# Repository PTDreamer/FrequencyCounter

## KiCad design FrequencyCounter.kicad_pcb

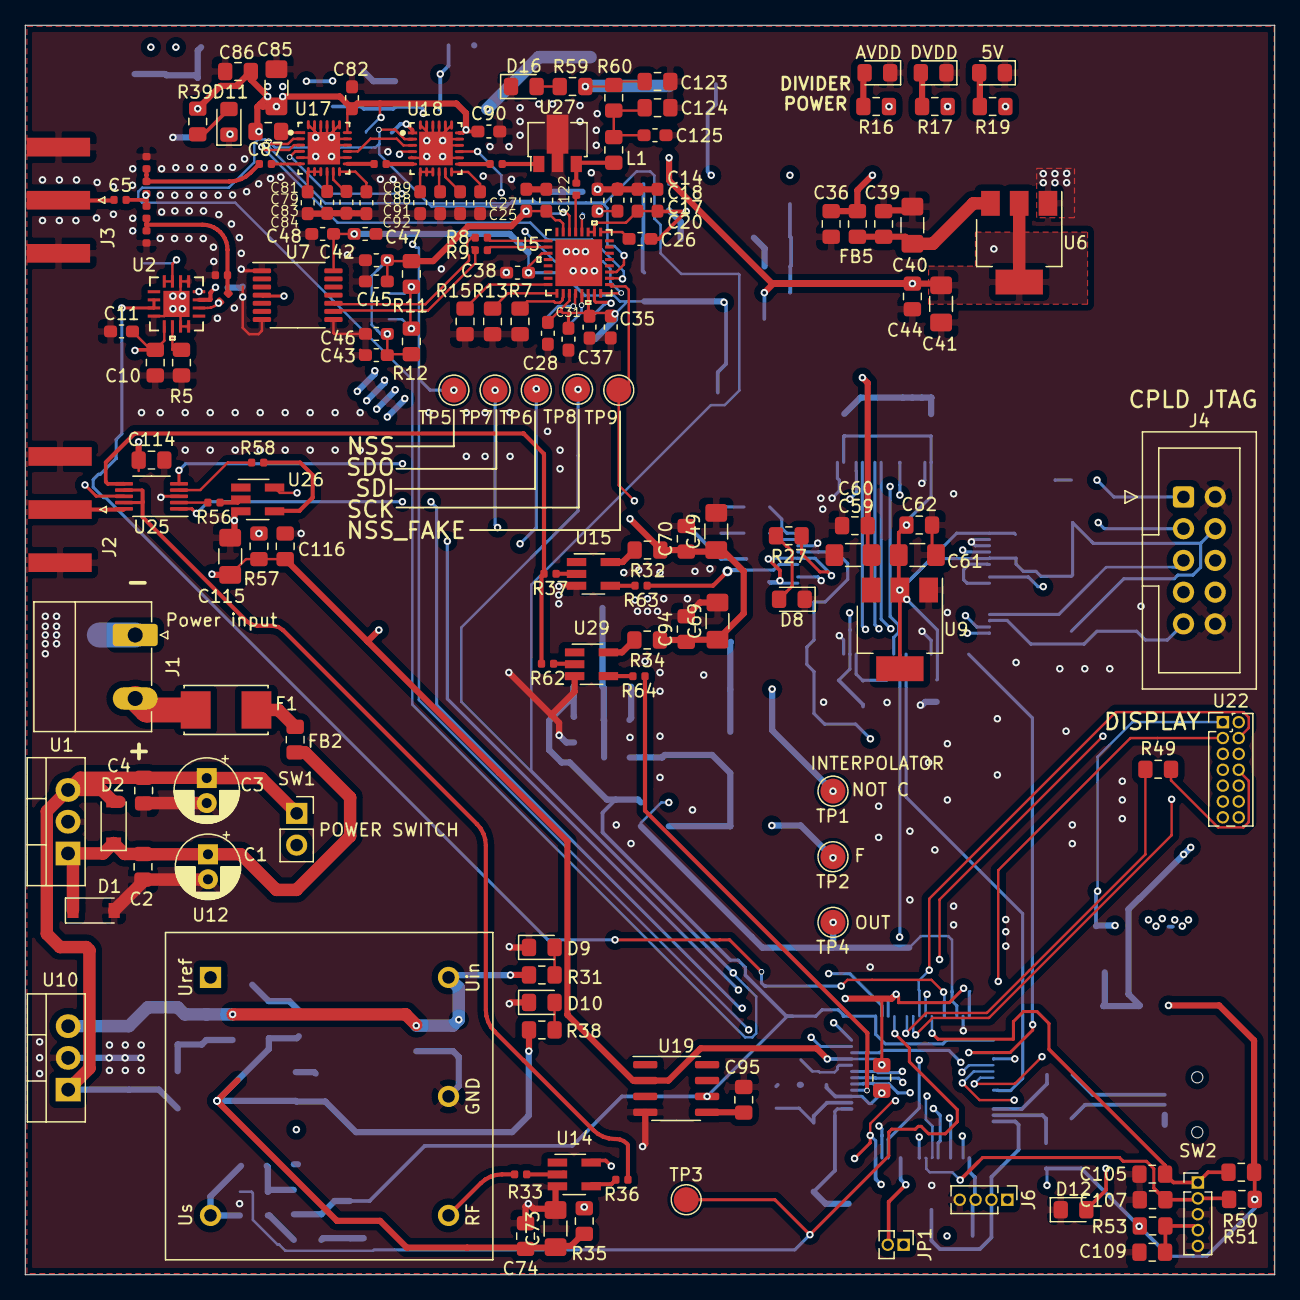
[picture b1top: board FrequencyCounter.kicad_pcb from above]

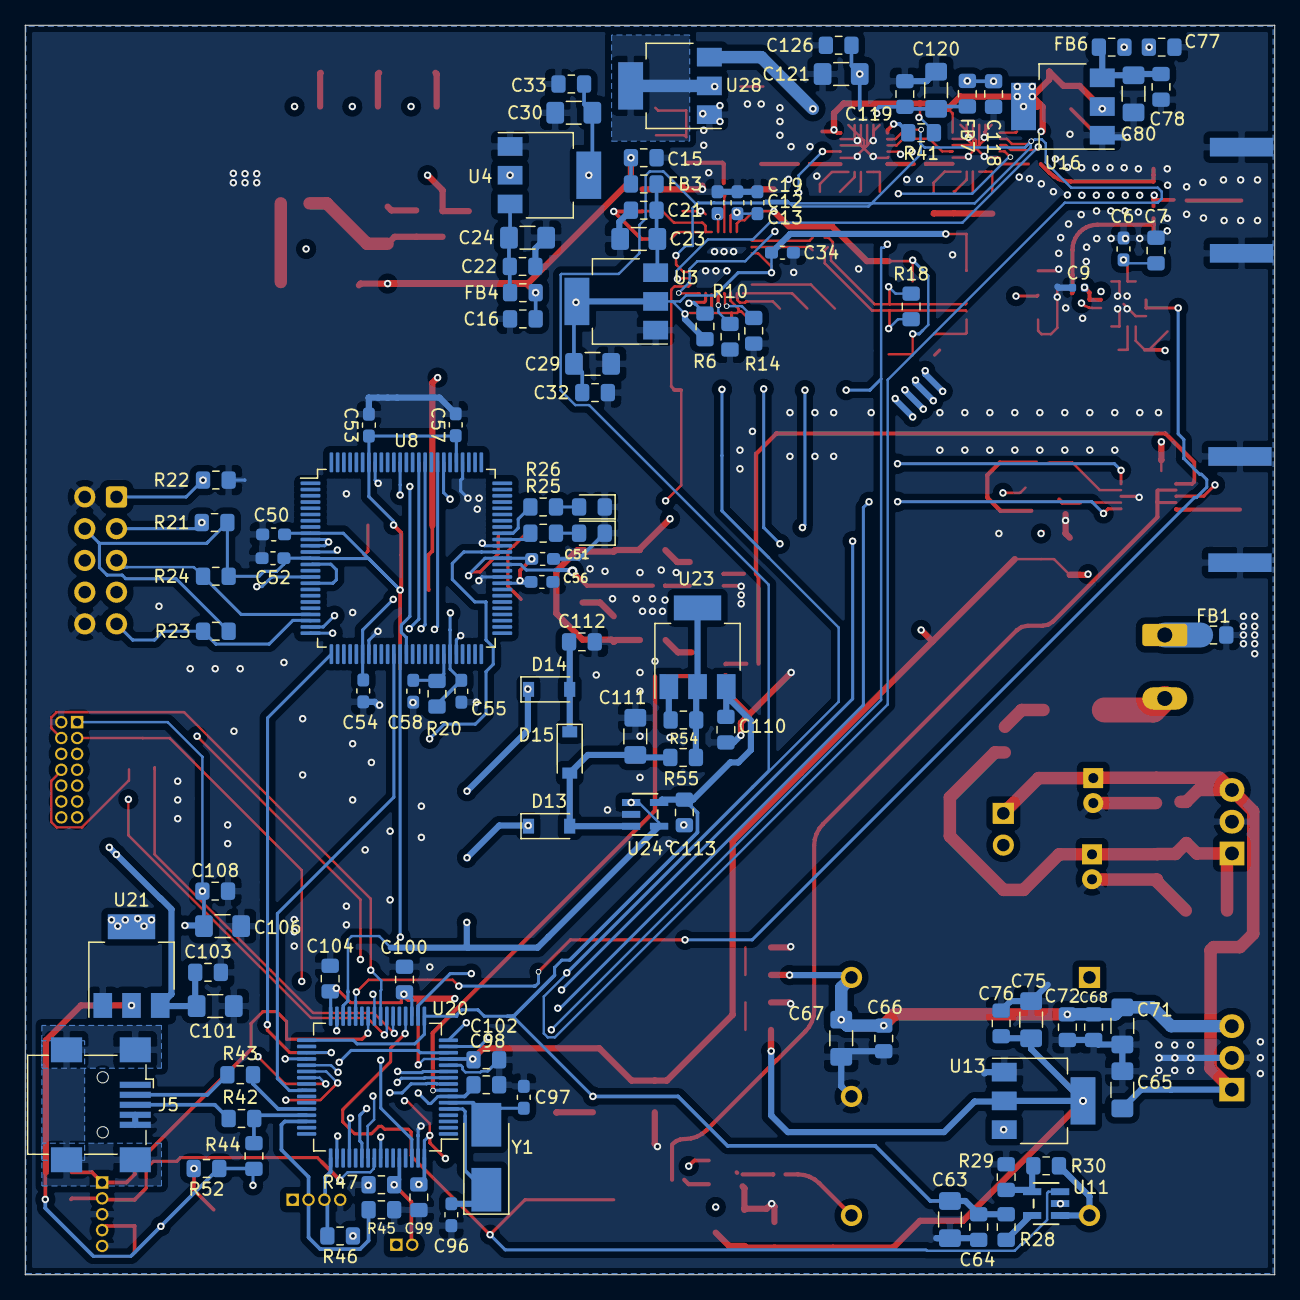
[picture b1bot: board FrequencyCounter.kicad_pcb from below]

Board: 4 copper layers, 100.0 x 100.0 mm, 263 parts (106 on the bottom side), 150 nets.

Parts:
C1, C3: 10u; CP_Radial_D5.0mm_P2.00mm
C2, C4: 10n; C_0805_2012Metric_Pad1.15x1.40mm_HandSolder
C5: 10n; C_0402_1005Metric
C6, C11, C13, C18, C19, C20, C27, C31, C35, C38: 100p; C_0603_1608Metric_Pad1.05x0.95mm_HandSolder
C7, C10, C15, C16, C21, C22, C32, C33, C36, C39, C44, C60, C62, C64, C66, C68, C70, C72, C74, C76, C77, C78, C86, C94, C98, C99, C100, C102, C103, C104, C108, C114, C116, C118, C119, C126: 0.1u; C_0805_2012Metric_Pad1.15x1.40mm_HandSolder
C8, C9: 1n; C_0402_1005Metric
C12, C14, C17, C25, C28, C34, C37, C42, C43, C47, C50, C51, C52, C53, C54, C55, C56, C57, C58: 0.1u; C_0603_1608Metric_Pad1.05x0.95mm_HandSolder
C23, C24, C29, C30, C40, C41, C80, C85, C120, C121: 10u; C_1206_3216Metric_Pad1.42x1.75mm_HandSolder
C26, C45, C46: 0.001u; C_0603_1608Metric_Pad1.05x0.95mm_HandSolder
C48: 0.01u; C_0603_1608Metric_Pad1.05x0.95mm_HandSolder
C49, C63, C67, C69, C73, C111, C115: 4.7u; C_1206_3216Metric_Pad1.42x1.75mm_HandSolder
C59, C61, C71, C75, C101, C106: 22u; C_1206_3216Metric_Pad1.42x1.75mm_HandSolder
C65: 0.33u; C_1206_3216Metric_Pad1.42x1.75mm_HandSolder
C79, C81, C83, C84, C88, C89, C91, C92: 330p; C_0603_1608Metric_Pad1.05x0.95mm_HandSolder
C82, C90: 1n; C_0603_1608Metric_Pad1.05x0.95mm_HandSolder
C87, C93: 330p; C_0402_1005Metric
C95, C110, C123: 1u; C_0805_2012Metric_Pad1.15x1.40mm_HandSolder
C96, C97: 8p; C_0603_1608Metric_Pad1.05x0.95mm_HandSolder
C105, C107, C109, C113: 100n; C_0805_2012Metric_Pad1.15x1.40mm_HandSolder
C112: 1n; C_0805_2012Metric_Pad1.15x1.40mm_HandSolder
C117, C122: 100n; C_0402_1005Metric
C124: 1.2n; C_0805_2012Metric_Pad1.15x1.40mm_HandSolder
C125: 68p; C_0603_1608Metric_Pad1.05x0.95mm_HandSolder
D1, D2: D; D_SOD-123
D3, D4, D5, D6, D7, D8, D9, D10, D11, D12, D16: LED; D_0805_2012Metric_Pad1.15x1.40mm_HandSolder
D13, D14, D15: 1N4148W; D_SOD-123
F1: Fuse; Fuseholder_Littelfuse_Nano2_157x
FB1, FB2, FB3, FB4, FB5, FB6, FB7: Ferrite_Bead; L_0805_2012Metric_Pad1.15x1.40mm_HandSolder
J1: Power input; PhoenixContact_MC_1,5_2-G-5.08_1x02_P5.08mm_Horizontal
J2: Ref_Imput; SMA_Amphenol_132289_EdgeMount
J3: Conn_Coaxial; SMA_Amphenol_132289_EdgeMount
J4: Microsemi_FlashPro-JTAG-10; IDC-Header_2x05_P2.54mm_Vertical
J5: USB_B_Micro; USB_Mini-B_Wuerth_65100516121_Horizontal
J6: SWD; PinHeader_1x04_P1.27mm_Vertical
JP1: Jumper_NO_Small; PinHeader_1x02_P1.27mm_Vertical
L1: 43nH; L_0805_2012Metric_Pad1.15x1.40mm_HandSolder
R1, R3: 1200; R_0402_1005Metric
R2: 4.12; R_0402_1005Metric
R4, R61: 52.3; R_0402_1005Metric
R5: 499; R_0805_2012Metric_Pad1.15x1.40mm_HandSolder
R6, R40, R41, R47: 100K; R_0805_2012Metric_Pad1.15x1.40mm_HandSolder
R7, R10, R13, R14, R15, R54: R; R_0805_2012Metric_Pad1.15x1.40mm_HandSolder
R8, R9: 24.9; R_0402_1005Metric
R11, R12: 75; R_0805_2012Metric_Pad1.15x1.40mm_HandSolder
R16, R17, R19, R25, R26, R27, R30, R38, R39, R49, R52, R59: 1K; R_0805_2012Metric_Pad1.15x1.40mm_HandSolder
R18: 100; R_0805_2012Metric_Pad1.15x1.40mm_HandSolder
R20, R21, R22, R23, R24, R45, R46, R48, R50, R51, R53: 10K; R_0805_2012Metric_Pad1.15x1.40mm_HandSolder
R28, R32, R34, R35, R57: 4.7; R_0805_2012Metric_Pad1.15x1.40mm_HandSolder
R29: 2K; R_0805_2012Metric_Pad1.15x1.40mm_HandSolder
R31: 1.8K; R_0805_2012Metric_Pad1.15x1.40mm_HandSolder
R33, R56: 49.9; R_0402_1005Metric
R36, R58, R63, R64: 33; R_0402_1005Metric
R37, R62: 100; R_0402_1005Metric
R42, R43: 20; R_0805_2012Metric_Pad1.15x1.40mm_HandSolder
R44: 1.5K; R_0805_2012Metric_Pad1.15x1.40mm_HandSolder
R55: 1R; R_0805_2012Metric_Pad1.15x1.40mm_HandSolder
R60: 0; R_0805_2012Metric_Pad1.15x1.40mm_HandSolder
SW1: SW_SPST; PinSocket_1x02_P2.54mm_Vertical
SW2: Rotary_Encoder_Switch; 1x5_1.27_rotary_encoder
TP1: INTPL_NC; TestPoint_Pad_D2.0mm
TP2: INTPL_F; TestPoint_Pad_D2.0mm
TP3: REF_ADJ_V; TestPoint_Pad_D2.0mm
TP4: INTPL_OUT; TestPoint_Pad_D2.0mm
TP5: SPI3_NSS; TestPoint_Pad_D2.0mm
TP6: SPI3_SDI; TestPoint_Pad_D2.0mm
TP7: SPI3_SDO; TestPoint_Pad_D2.0mm
TP8: SPI3_SCK; TestPoint_Pad_D2.0mm
TP9: SPI3_NSS_FAKE; TestPoint_Pad_D2.0mm
U1: LM7810_TO220; TO-220-3_Vertical
U2: AD8318ACPZ-REEL7
U3, U4, U16: LM1117-3.3; SOT-223-3_TabPin2
U5: HMC983LP5E
U6, U28: LM1117-5.0; SOT-223-3_TabPin2
U7: DS90LV019TMTC_NOPB; TSSOP-14_4.4x5mm_P0.65mm
U8: EPM240T100; LQFP-100_14x14mm_P0.5mm
U9, U13, U21: AMS1117-3.3; SOT-223-3_TabPin2
U10: LM7805_TO220; TO-220-3_Vertical
U11, U24: OPA365AIDBVT
U12: MV267; Oscillator_OCXO_Morion_MV317
U14, U15, U26, U29: NC7SZ04M5X; SOT-23-5_HandSoldering
U17, U18: HMC624ALP4E; Analog_Devices_Inc-CP-24-16-12_2017-C-0
U19: REF5025ID; SOIC-8_3.9x4.9mm_P1.27mm
U20: STM32F373R8Tx; LQFP-64_10x10mm_P0.5mm
U22: CR2013-MI2120; PinHeader_2x07_P1.27mm_Vertical
U23: LT3080xST; SOT-223
U25: TS5A23159DGS; VSSOP-10_3x3mm_P0.5mm
U27: ADL5610; SOT-89-3
Y1: 8MHz; Crystal_SMD_5032-2Pin_5.0x3.2mm_HandSoldering

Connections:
+3V3: C73.1, C74.1, C75.1, C76.1, R35.1, R38.1, U13.2
+3V3_processor: C49.1, C69.1, C70.1, C94.1, C99.1, C100.1, C102.1, C104.1, C106.1, C108.1, C114.1, C115.1, C116.1, J6.1, JP1.1, R32.1, R34.1, R44.1, R46.1, R48.1, R50.1, R51.1, R52.1, R53.1, R57.1, U19.2, U20.13, U20.19, U20.32, U20.64, U21.2, U22.1, U25.8
+5V: C66.1, C67.1, C68.1, C71.1, C72.1, R31.1, U10.3, U12.5, U13.3
/VCC: C36.1, C59.1, C60.1, C77.1, C101.1, C103.1, C118.1, FB5.1, FB6.1, FB7.1, SW1.2, U9.3, U21.3
/VCC_ALWAYS_ON: C3.1, C4.1, C65.1, D2.2, SW1.1, U1.3, U10.1
/amplifier/RF_IN: C117.2, U18.13
/attenuator/ATTEN1_SERIN: TP6.1, U5.2, U17.3, U20.18
/attenuator/ATTEN1_SEROUT: U17.15, U18.3
/attenuator/ATTEN2_SEROUT: TP7.1, U5.32, U18.15, U20.16
/attenuator/ATTEN_CLK: TP8.1, U5.3, U17.2, U18.2, U20.15
/attenuator/ATTEN_LE: TP5.1, U17.4, U18.4, U20.50
/attenuator/RF_IN: C87.1, R1.2, R2.2
/attenuator/VDD: C82.1, C85.1, C86.1, C90.1, R39.1, R40.1, R41.1, U16.2, U17.18, U18.18
/divider/5V: C15.1, C16.1, C25.1, C27.1, C41.1, C42.1, C43.1, C44.1, C45.1, C46.1, FB3.1, FB4.1, R11.2, R12.1, R19.1, U5.15, U6.2
/divider/AVDD: C12.1, C13.1, C14.1, C17.1, C18.1, C20.1, C26.2, C30.1, C33.1, R16.1, U4.2, U5.10, U5.11, U5.14
/divider/DVDD: C28.1, C29.1, C31.1, C32.1, C34.1, C35.1, C37.1, C38.1, C47.1, C48.1, R6.1, R17.1, U3.2, U5.19, U5.27, U5.30, U7.14
/divider/INPUT: C122.1, U5.13
/divider/OUT: U7.4, U8.38
/divider/SENB: TP9.1, U5.1, U20.55
/divider/div_clk_N: R8.2, U5.17
/divider/div_clk_P: R9.2, U5.18
/divider/div_clkr_N: R8.1, R11.1, R18.1, U7.10
/divider/div_clkr_P: R9.1, R12.2, R18.2, U7.9
/fpga/3.3V: C50.1, C51.1, C52.1, C53.1, C54.1, C55.1, C56.1, C57.1, C61.1, C62.1, J4.4, R20.1, R21.1, R23.1, R24.1, R27.1, U8.9, U8.13, U8.31, U8.45, U8.59, U8.63, U8.80, U8.94, U9.2
/fpga/icp0: U8.26, U20.35
/fpga/refclk: R63.1, U8.62
/fpga/sigclk: U8.14, U8.17
/frequency_ref/3.3V_ref_in: C63.1, C64.1, C110.1, C113.1, R28.1, U19.6, U20.17, U20.33, U23.3, U24.5
/frequency_ref/10MHz: R36.1, U25.7, U25.9
/interpolator/f: D13.1, TP2.1, U8.82
/interpolator/int_out: TP4.1, U20.30, U24.1, U24.4
/interpolator/not_c: D14.1, TP1.1, U8.89
/logdetector/5V_in: C6.2, C7.2, C10.2, C11.2, C121.1, C123.2, C126.1, R59.1, R60.1, U2.3, U2.4, U2.9, U2.16, U28.2
/logdetector/RF_INPUT: C8.1, R3.1, R4.1, R61.2
/processor/ADC1: U2.6, U2.7, U20.28
/processor/CLK_OUT: U8.36, U20.41
/processor/DAC1: TP3.1, U11.3, U20.20
/processor/DAC2_OUT1: R49.1, U20.22
/processor/LCD_DC: U20.25, U22.5
/processor/LCD_RESET: U20.24, U22.4
/processor/MODESHIFT: U8.16, U20.57
/processor/SPI1_CLK: U20.38, U22.7
/processor/SPI1_MISO: U20.39, U22.6
/processor/SPI1_NSS: U20.37, U22.3
/processor/SPI2_CLK: U8.12, U20.36
/processor/SPI2_MISO: U8.37, U20.10
/processor/SPI2_MOSI: U8.86, U20.11
/processor/SPI2_NSS: U8.64, U20.62
/processor/SWD_CLK: J6.3, R46.2, U20.49
/processor/SWD_IO: J6.2, R45.1, U20.46
/processor/TIM2_ETR: U8.85, U20.14
/processor/TIM3_CH1: C107.1, R51.2, SW2.B, U20.56
/processor/TIM3_CH2: C105.1, R50.2, SW2.A, U20.26
/processor/TIM5_CH2: U8.83, U20.9
/processor/TIM5_ETR: R64.1, U20.8
/processor/USB_DM: R43.1, U20.44
/processor/USB_DP: R42.1, R44.2, U20.45
/ref_input_output/ctr_0: U20.54, U25.5
/ref_input_output/ctr_1: U20.52, U25.1
/ref_input_output/rf2: R56.2, U25.2
/ref_input_output/rf22: R56.1, U26.2
/ref_input_output/rf_input_output: J2.1, U25.10
/ref_input_output/rf_out: R37.2, R62.2, U25.6
GND: C1.2, C2.2, C3.2, C4.2, C6.1, C7.1, C9.1, C10.1, C11.1, C12.2, C13.2, C14.2, C15.2, C16.2, C17.2, C18.2, C19.2, C20.2, C21.2, C22.2, C23.2, C24.2, C25.2, C27.2, C28.2, C29.2, C30.2, C31.2, C32.2, C33.2, C34.2, C35.2, C36.2, C37.2, C38.2, C39.2, C40.2, C41.2, C42.2, C43.2, C44.2, C45.2, C46.2, C47.2, C48.2, C49.2, C50.2, C51.2, C52.2, C53.2, C54.2, C55.2, C56.2, C57.2, C58.2, C59.2, C60.2, C61.2, C62.2, C63.2, C64.2, C65.2, C66.2, C67.2, C68.2, C69.2, C70.2, C71.2, C72.2, C73.2, C74.2, C75.2, C76.2, C77.2, C78.2, C79.2, C80.2, C81.2, C82.2, C83.2, C84.2, C85.2, C86.2, C88.2, C89.2, C90.2, C91.2, C92.2, C94.2, C95.2, C96.2, C97.2, C98.1, C99.2, C100.2, C101.2, C102.2, C103.2, C104.2, C105.2, C106.2, C107.2, C108.2, C109.2, C110.2, C111.2, C112.2, C113.2, C114.2, C115.2, C116.2, C118.2, C119.2, C120.2, C121.2, C123.1, C124.1, C125.1, C126.2, D1.2, D3.1, D4.1, D5.1, D6.1, D7.1, D8.1, D9.1, D10.1, D11.1, D12.1, D16.1, FB1.1, J2.2, J3.2, J4.2, J4.10, J5.4, J5.5, J6.4, R1.1, R4.2, R5.2, R7.2, R10.2, R13.2, R14.2, R15.2, R22.1, R29.2, R45.2, R47.2, R61.1, SW2.C, SW2.S2, U1.2, U2.1, U2.2, U2.8, U2.11, U2.12, U2.17, U3.1, U4.1, U5.33, U6.1, U7.1, U7.7, U7.8, U8.10, U8.11, U8.32, U8.46, U8.60, U8.65, U8.79, U8.93, U9.1, U10.2, U11.2, U12.4, U13.1, U14.3, U15.3, U16.1, U17.5, U17.14, U17.16, U17.17, U17.19, U17.20, U17.21, U17.22, U17.23, U17.24, U17.25, U18.5, U18.14, U18.16, U18.17, U18.19, U18.20, U18.21, U18.22, U18.23, U18.24, U18.25, U19.4, U20.12, U20.31, U20.63, U21.1, U22.2, U24.2, U25.3, U26.3, U27.2, U28.1, U29.3
unnamed: C1.1, C2.1, D1.1, D2.1, FB2.1, U1.1
unnamed: C5.1, J3.1
unnamed: C5.2, R2.1, R3.2
unnamed: C8.2, U2.14
unnamed: C9.2, U2.15
unnamed: C19.1, U5.12
unnamed: C21.1, C23.1, FB3.2, U3.3
unnamed: C22.1, C24.1, FB4.2, U4.3
unnamed: C26.1, U5.9
unnamed: C39.1, C40.1, FB5.2, U6.3
unnamed: C58.1, R20.2, U8.44
unnamed: C78.1, C80.1, FB6.2, U16.3
unnamed: C79.1, U17.10
unnamed: C81.1, U17.7, U17.8, U17.9
unnamed: C83.1, U17.11
unnamed: C84.1, U17.12
unnamed: C87.2, U17.6
unnamed: C88.1, U18.10
unnamed: C89.1, U18.7, U18.8, U18.9
unnamed: C91.1, U18.11
unnamed: C92.1, U18.12
unnamed: C93.1, U18.6
unnamed: C93.2, U17.13
unnamed: C95.1, U19.5
unnamed: C96.1, U20.5, Y1.1
unnamed: C97.1, U20.6, Y1.2
unnamed: C98.2, R48.2, U20.7
unnamed: C109.1, R53.2, SW2.S1
unnamed: C111.1, D13.2, D15.2, R55.1, U24.3
unnamed: C112.1, D14.2, D15.1
unnamed: C117.1, U27.1
unnamed: C119.1, C120.1, FB7.2, U28.3
unnamed: C122.2, L1.2, U27.3
unnamed: C124.2, C125.2, L1.1, R60.2
unnamed: D3.2, R16.2
unnamed: D4.2, R17.2
unnamed: D5.2, R19.2
unnamed: D6.2, R25.2
unnamed: D7.2, R26.2
unnamed: D8.2, R27.2
unnamed: D9.2, R31.2
unnamed: D10.2, R38.2
unnamed: D11.2, R39.2
unnamed: D12.2, R52.2
unnamed: D16.2, R59.2
unnamed: F1.1, FB2.2
unnamed: F1.2, J1.2
unnamed: FB1.2, J1.1
unnamed: J4.1, R22.2, U8.24
unnamed: J4.3, R21.2, U8.25
unnamed: J4.5, R24.2, U8.22
unnamed: J4.9, R23.2, U8.23
unnamed: J5.2, R43.2
unnamed: J5.3, R42.2
unnamed: JP1.2, R47.1, U20.60
unnamed: R5.1, U2.10
unnamed: R6.2, U5.31
unnamed: R7.1, U5.26
unnamed: R10.1, U5.29
unnamed: R13.1, U5.25
unnamed: R14.1, U5.28
unnamed: R15.1, U5.24
unnamed: R25.1, U8.67
unnamed: R26.1, U8.66
unnamed: R28.2, U11.5
unnamed: R29.1, R30.1, U11.4
unnamed: R30.2, U11.1, U12.2
unnamed: R32.2, U15.5
unnamed: R33.1, U14.2
unnamed: R33.2, U12.3
unnamed: R34.2, U29.5
unnamed: R35.2, U14.5
unnamed: R36.2, U14.4
unnamed: R37.1, U15.2
unnamed: R40.2, U17.1
unnamed: R41.2, U18.1
unnamed: R49.2, U22.8
unnamed: R54.1, R55.2, U23.2, U23.4
unnamed: R54.2, U23.1
unnamed: R57.2, U26.5
unnamed: R58.1, U25.4
unnamed: R58.2, U26.4
unnamed: R62.1, U29.2
unnamed: R63.2, U15.4
unnamed: R64.2, U29.4
unnamed: U20.23, U22.9

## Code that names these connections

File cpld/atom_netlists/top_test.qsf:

set_instance_assignment -name IO_STANDARD "3.3-V LVTTL" -to sigclk
set_location_assignment PIN_77 -to led
set_location_assignment PIN_4 -to icp1
set_location_assignment PIN_2 -to int1
set_location_assignment PIN_68 -to led2
set_location_assignment PIN_15 -to miso
set_location_assignment PIN_95 -to modeshift
set_location_assignment PIN_92 -to mosi
set_location_assignment PIN_16 -to rampstartP
set_location_assignment PIN_3 -to rampstopN
set_location_assignment PIN_12 -to refclk
set_location_assignment PIN_62 -to sck
set_location_assignment PIN_14 -to sigclk
set_location_assignment PIN_5 -to sigin1
set_location_assignment PIN_96 -to sigin2
set_location_assignment PIN_97 -to sigout
set_location_assignment PIN_64 -to ss
set_location_assignment PIN_17 -to icp0
set_global_assignment -name FAMILY "MAX II"
set_global_assignment -name DEVICE EPM240T100C5
set_global_assignment -name TOP_LEVEL_ENTITY top
set_global_assignment -name ORIGINAL_QUARTUS_VERSION 20.1.0
set_global_assignment -name PROJECT_CREATION_TIME_DATE "23:55:24  AUGUST 21, 2020"
set_global_assignment -name LAST_QUARTUS_VERSION "20.1.0 Lite Edition"
set_global_assignment -name PROJECT_OUTPUT_DIRECTORY output_files
set_global_assignment -name MIN_CORE_JUNCTION_TEMP 0
set_global_assignment -name MAX_CORE_JUNCTION_TEMP 85
set_global_assignment -name ERROR_CHECK_FREQUENCY_DIVISOR "-1"
set_global_assignment -name POWER_EXT_SUPPLY_VOLTAGE_TO_REGULATOR 3.3V
set_global_assignment -name VHDL_FILE top.vhd
set_global_assignment -name AUTO_RESTART_CONFIGURATION OFF
set_global_assignment -name ENABLE_DEVICE_WIDE_RESET ON
set_global_assignment -name ENABLE_DEVICE_WIDE_OE ON
set_global_assignment -name ENABLE_OCT_DONE OFF
set_global_assignment -name ENABLE_CONFIGURATION_PINS OFF
set_global_assignment -name ENABLE_BOOT_SEL_PIN OFF
set_global_assignment -name USE_CONFIGURATION_DEVICE ON
set_global_assignment -name RESERVE_ALL_UNUSED_PINS "AS INPUT TRI-STATED WITH WEAK PULL-UP"
set_global_assignment -name POWER_PRESET_COOLING_SOLUTION "NO HEAT SINK WITH STILL AIR"
set_global_assignment -name EDA_SIMULATION_TOOL "ModelSim-Altera (Verilog)"
set_global_assignment -name EDA_TIME_SCALE "1 ps" -section_id eda_simulation
set_global_assignment -name EDA_OUTPUT_DATA_FORMAT "VERILOG HDL" -section_id eda_simulation
set_global_assignment -name EDA_GENERATE_FUNCTIONAL_NETLIST OFF -section_id eda_board_design_timing
set_global_assignment -name EDA_GENERATE_FUNCTIONAL_NETLIST OFF -section_id eda_board_design_symbol
set_global_assignment -name EDA_GENERATE_FUNCTIONAL_NETLIST OFF -section_id eda_board_design_signal_integrity
set_global_assignment -name EDA_GENERATE_FUNCTIONAL_NETLIST OFF -section_id eda_board_design_boundary_scan
set_global_assignment -name VECTOR_WAVEFORM_FILE Waveform.vwf

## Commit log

2021-09-11 Add license

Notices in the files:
parts and their libraries:
Copyright 2016 Accelerated Designs. All rights reserved.
